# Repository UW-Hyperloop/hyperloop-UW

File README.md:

# Hyperloop UW

Feel free to make necessary changes.  

washingtonhyperloop.squarespace.com

If this is your first time in this repo, add your name to member list and remember to pull regularly.

**Contributor list:**   
Daniel Nordgen  
Kaito Yan  
Nahush Shrivatsa  
Alexandra Yankovskaya
Hemil K. Patel

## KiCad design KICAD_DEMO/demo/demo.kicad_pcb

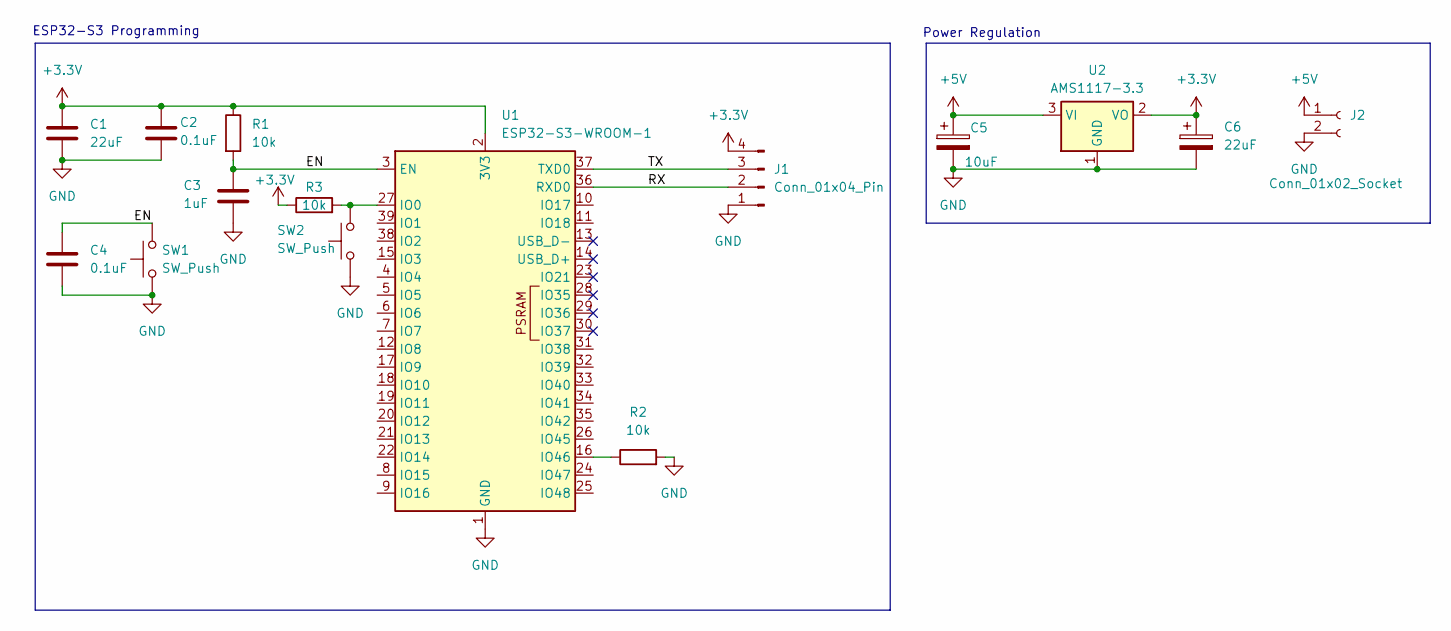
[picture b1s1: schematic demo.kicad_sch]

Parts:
C1, C6: 22uF; C_0805_2012Metric_Pad1.18x1.45mm_HandSolder
C2, C4: 0.1uF; C_0603_1608Metric_Pad1.08x0.95mm_HandSolder
C3: 1uF; C_0603_1608Metric_Pad1.08x0.95mm_HandSolder
C5: 10uF; C_0805_2012Metric_Pad1.18x1.45mm_HandSolder
J1: Conn_01x04_Pin; PinSocket_1x04_P2.54mm_Vertical
J2: Conn_01x02_Socket; PinSocket_1x02_P2.54mm_Vertical
R1, R2, R3: 10k; R_0402_1005Metric_Pad0.72x0.64mm_HandSolder
SW1, SW2: SW_Push; SW_Push_1P1T_NO_CK_KMR2
U1: ESP32-S3-WROOM-1
U2: AMS1117-3.3; SOT-223-3_TabPin2

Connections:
+3.3V: C1.1, C2.1, C6.1, J1.4, R1.1, R3.1, U1.2 (3V3), U2.2 (VO)
+5V: C5.1, J2.1, U2.3 (VI)
/EN: C3.1, C4.1, R1.2, SW1.2, U1.3 (EN)
/RX: J1.2, U1.36 (RXD0)
/TX: J1.3, U1.37 (TXD0)
GND: C1.2, C2.2, C3.2, C4.2, C5.2, C6.2, J1.1, J2.2, R2.2, SW1.1, SW2.1, U1.1 (GND), U1.40 (GND), U1.41 (GND), U2.1 (GND)
unnamed: R3.2, SW2.2, U1.27 (IO0)
unnamed: R2.1, U1.16 (IO46)

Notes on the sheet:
Power Regulation
ESP32-S3 Programming

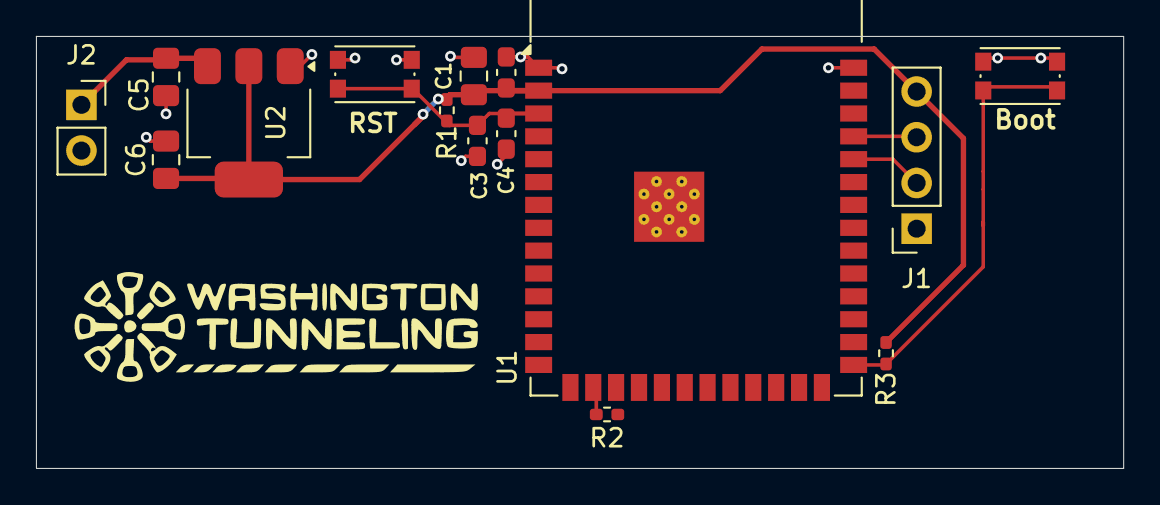
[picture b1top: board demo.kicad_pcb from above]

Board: 2 copper layers, 60.4 x 24.0 mm, 15 parts (0 on the bottom side), 8 nets.

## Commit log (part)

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2023-12-08 Update tbm0.ino for drive
    Can control drive inputs through serial monitor
2024-10-22 remove sensors
2024-10-22 oops
2024-10-28 Update tbm.h
    commented motor out and pump out since we are considering constant speed for pump, and the motor is decided to be constant speed
2024-10-30 Simple datastore server
2024-11-19 fixed circular meter can't start at nonzero bug
2024-11-19 Save before transitioning to different Design idea
2024-11-19 added contactor symbol
2024-11-19 tbm1.ino set up
2024-11-19 added files for organization
2024-11-19 src folder
2025-01-16 reorganized
2025-01-16 Update state.ino
    Cleaned up some of sasha's work and it compiles now.
2025-01-16 Update sensors.ino
    Cleaned up and compiles now. Tegbir is working on this though so it might all get replaced anyways lol
2025-01-16 server folder
2025-01-16 Initial json payload program
2025-01-17 updated gui
2025-01-17 added flow rate sensor draft and e stop draft
2025-01-18 global var SystemData
2025-01-20 add config + init state
2025-01-21 Update server.py
    TCP Server for sending and receiving
2025-01-23 sensor updates
2025-01-23 Updated state.ino to include E-stop button
2025-01-27 Function calls
2025-01-27 More function calls
2025-01-28 init nahush branch
2025-01-28 tbm_init + config
2025-01-30 .h file guard and #include syntax
2025-01-30 small change
2025-01-30 Updated messages to be sent from TBM to server and vice versa
2025-01-30 integrated max31855 get temperature code into sensors, need to finalize pin selecction
2025-02-01 Compiled everything!
2025-02-01 complete merge resolution?
2025-02-01 estop logic and remove flow
2025-02-04 tbm stop, start, data
2025-02-04 compile everything
2025-02-06 Update tbm.h to not have a error state anymore
2025-02-08 updating GUI for state, starting setting up framework for sever communication.
2025-02-08 Added stale value indicator to motor temp meter, have not added to other meters.
2025-02-08 temp and button logic for estop
2025-02-11 estopctrl -> estopsense
2025-02-11 Removed unused components, added new version of flow meter
2025-02-11 estop circuit works
2025-02-11 json parsing cleaned up
2025-02-13 edited keyboard logic in server
2025-02-15 Server to GUI com ideas
2025-02-19 gg lol
2025-02-20 firmware refactoring
2025-02-22 ESP32 to GUI end to end testing verified, GUI can start and stop ESP, and can display updated info about esp
2025-02-25 Update sensors.ino to include gas sensor
    Gas sensor in readSensors() commented out for the time being.
2025-02-25 Update jsonSerialization.ino to include gas sensor and changed pump power to pump temp
2025-02-25 Update tbm.h to include gas sensor and pump temp
2025-02-25 estop msgs
2025-02-25 server
2025-02-27 updated server to handle sending estop message to GUI, GUI updated to handle message
2025-02-27 updated server to send estop message to GUI. GUI updated to handle message
2025-03-01 correct flush
2025-03-01 changes to connect server and gui when on different machines
2025-03-06 finished pump temp update
2025-03-06 estop fix
2025-03-10 some updates on gui
2025-03-10 more gui updates
2025-03-11 finished adding bentonite pump button, gas sensor. removed water pump temp.
2025-03-11 Update tbm.h to include gas sensor
2025-03-11 Update sensors.ino to include gas sensor
    to - do: fix gas sensor constants on Lines 132 - 134
2025-03-11 Update jsonSerialization.ino to include gas sensor
2025-03-13 added draft gas_ppm input from server json in GUI
2025-03-13 Create sending_ESP_comms
2025-03-13 added receiving ESP code to tbm1
2025-03-15 Update sending_ESP_comms.ino to include temp sensor and gas sensor
2025-03-15 power_failure and comms failure added
2025-03-15 updated sending and receiving ESP files
2025-03-15 minor change
2025-03-21 added receiver code
2025-05-15 kicad demo
2025-05-30 hyperloop logo
